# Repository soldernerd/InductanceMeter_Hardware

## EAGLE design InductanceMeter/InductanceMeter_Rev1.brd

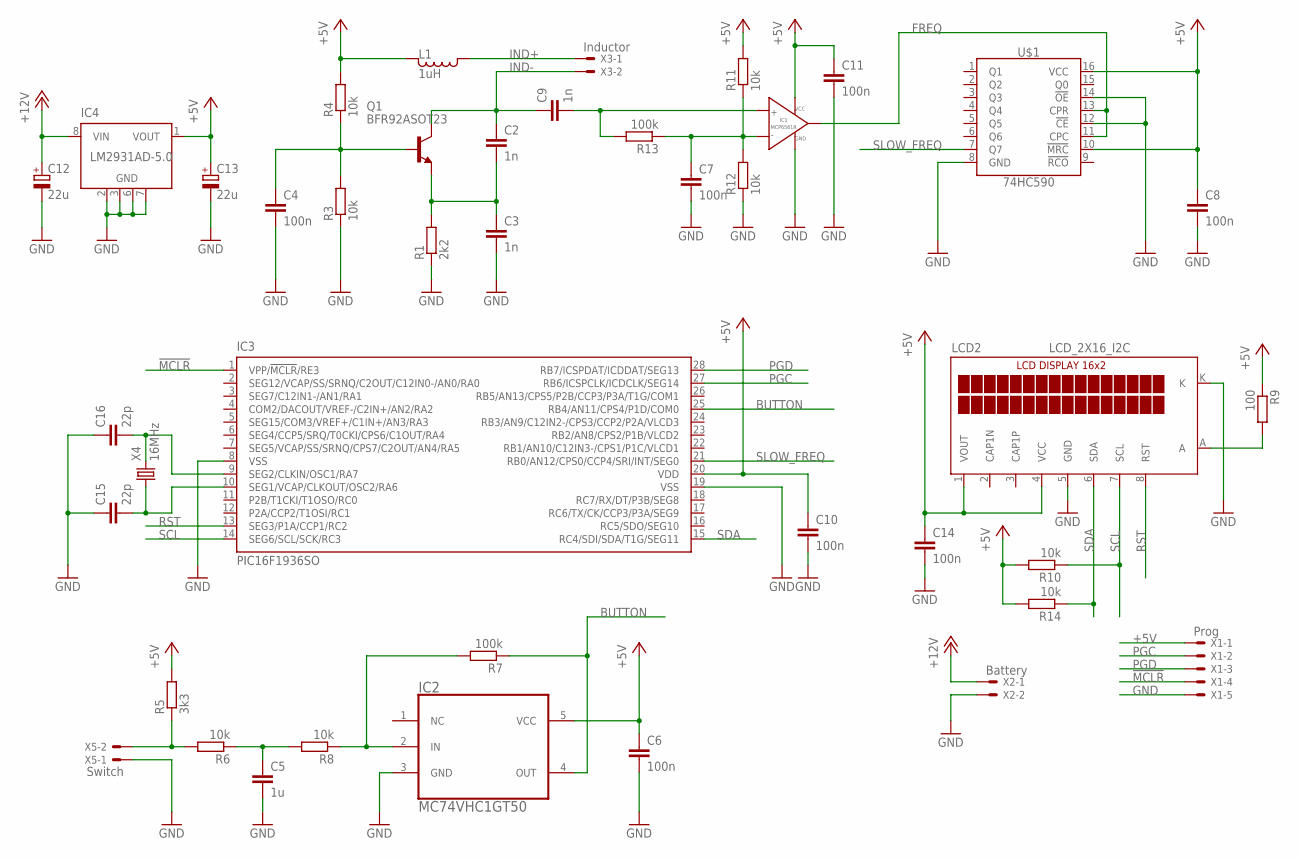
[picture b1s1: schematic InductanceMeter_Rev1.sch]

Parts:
C2, C3, C9: 1n; C0805
C4, C6, C7, C8, C10, C11, C14: 100n; C0805
C5: 1u; C0805
C12, C13: 22u; SMC_C
C15, C16: 22p; C0805
IC1: MCP6561R; SOT-23-5
IC2: MC74VHC1GT50; SOT-23-5
IC3: PIC16F1936SO; SO28W
IC4: LM2931AD-5.0; SO8
L1: 1uH; L0805
LCD2: LCD_2X16_I2C
Q1: BFR92ASOT23; SOT23
R1: 2k2; R0805
R3, R4, R6, R8, R10, R11, R12, R14: 10k; R0805
R5: 3k3; R0805
R7, R13: 100k; R0805
R9: 100; R0805
U$1: 74HC590; SO16
X1: Prog; 22-23-2051
X2: Battery; 22-23-2021
X3: Inductor; 22-23-2021
X4: 16MHz; CSM-7X-DU
X5: Switch; 22-23-2021

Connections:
!MCLR!: IC3.1 (VPP/!MCLR!/RE3), X1.4
+5V: C6.1, C8.1, C10.1, C11.1, C13.+, C14.1, IC1.2 (VCC), IC2.5 (VCC), IC3.20 (VDD), IC4.1 (VOUT), L1.2, LCD2.1 (VOUT), LCD2.4 (VCC), R4.2, R5.2, R9.1, R10.2, R11.2, R14.2, U$1.10 (!MRC!), U$1.16 (VCC), X1.1
+12V: C12.+, IC4.8 (VIN), X2.1
BUTTON: IC2.4 (OUT), IC3.25 (RB4/AN11/CPS4/P1D/COM0), R7.1
FREQ: IC1.1 (VOUT), U$1.11 (CPC), U$1.13 (CPR)
GND: C3.2, C4.2, C5.2, C6.2, C7.2, C8.2, C10.2, C11.2, C12.-, C13.-, C14.2, C15.1, C16.1, IC1.5 (GND), IC2.3 (GND), IC3.8 (VSS), IC3.19 (VSS), IC4.2 (GND), IC4.3 (GND), IC4.6 (GND), IC4.7 (GND), LCD2.5 (GND), LCD2.K, R1.1, R3.1, R12.1, U$1.8 (GND), U$1.12 (!CE!), U$1.14 (!OE!), X1.5, X2.2, X5.1
IND+: L1.1, X3.1
IND-: C2.1, C9.1, Q1.3 (C), X3.2
unnamed: C16.2, IC3.9 (SEG2/CLKIN/OSC1/RA7), X4.2
unnamed: C2.2, C3.1, Q1.2 (E), R1.2
unnamed: C4.1, Q1.1 (B), R3.2, R4.1
unnamed: LCD2.A, R9.2
unnamed: C5.1, R6.1, R8.2
unnamed: R5.1, R6.2, X5.2
unnamed: IC2.2 (IN), R7.2, R8.1
unnamed: C15.2, IC3.10 (SEG1/VCAP/CLKOUT/OSC2/RA6), X4.1
unnamed: C7.1, IC1.4 (VIN-), R11.1, R12.2, R13.1
unnamed: C9.2, IC1.3 (VIN+), R13.2
PGC: IC3.27 (RB6/ICSPCLK/ICDCLK/SEG14), X1.2
PGD: IC3.28 (RB7/ICSPDAT/ICDDAT/SEG13), X1.3
RST: IC3.13 (SEG3/P1A/CCP1/RC2), LCD2.8 (RST)
SCL: IC3.14 (SEG6/SCL/SCK/RC3), LCD2.7 (SCL), R10.1
SDA: IC3.15 (RC4/SDI/SDA/T1G/SEG11), LCD2.6 (SDA), R14.1
SLOW_FREQ: IC3.21 (RB0/AN12/CPS0/CCP4/SRI/INT/SEG0), U$1.7 (Q7)

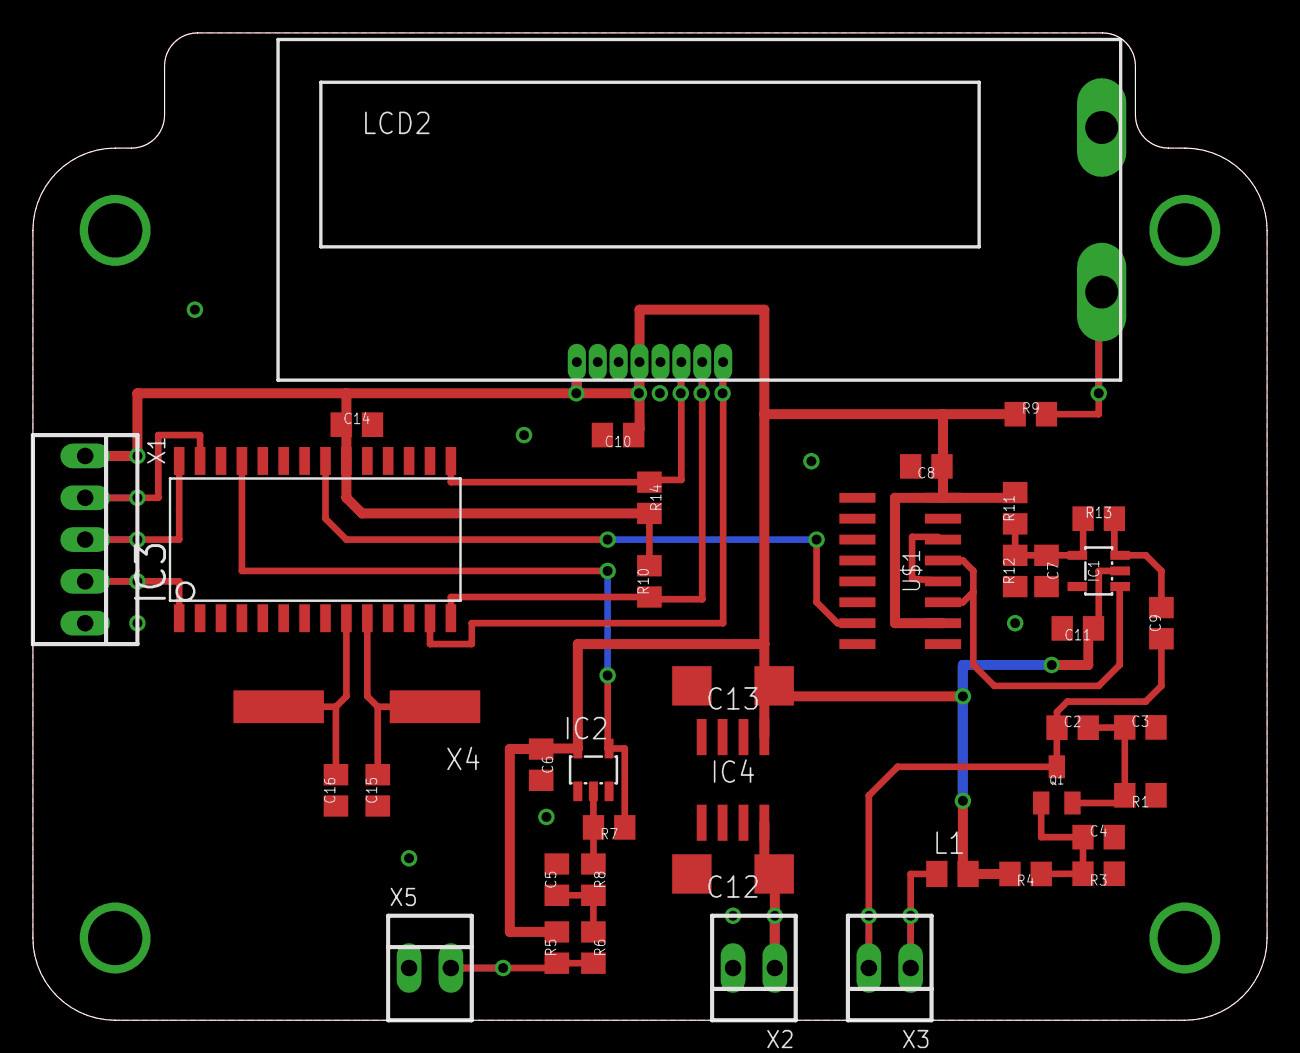
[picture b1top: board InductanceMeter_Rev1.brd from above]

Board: 2 copper layers, 75.0 x 60.0 mm, 41 parts (0 on the bottom side), 24 nets.

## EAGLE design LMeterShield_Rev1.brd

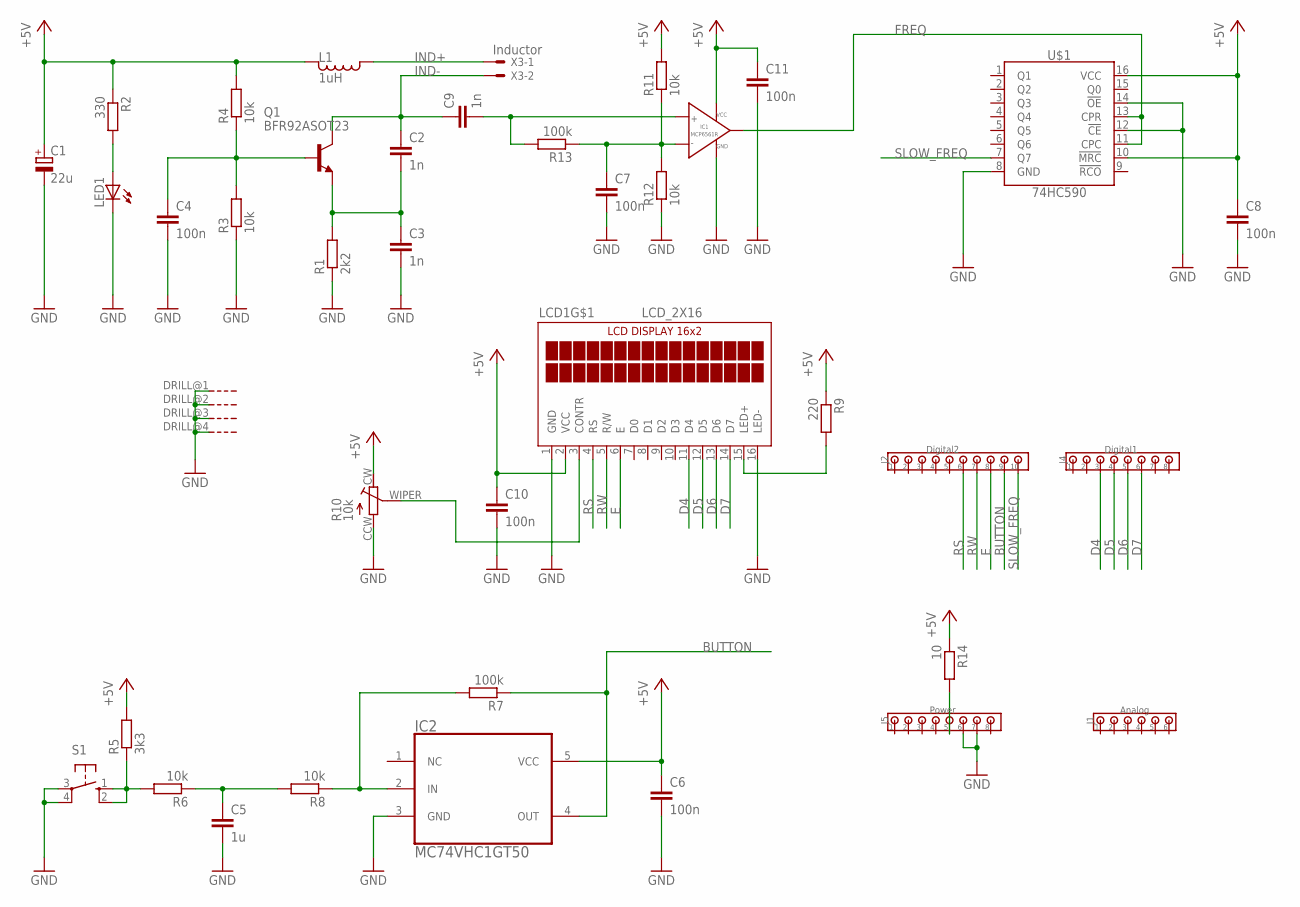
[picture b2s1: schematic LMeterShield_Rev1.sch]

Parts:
C1: 22u; SMC_C
C2, C3, C9: 1n; C0805
C4, C6, C7, C8, C10, C11: 100n; C0805
C5: 1u; C0805
IC1: MCP6561R; SOT-23-5
IC2: MC74VHC1GT50; SOT-23-5
J1: Analog; 100MIL_6X_ROUND
J2: Digital2; 100MIL_10X_ROUND
J4: Digital1; 100MIL_8X_ROUND
J5: Power; 100MIL_8X_ROUND
L1: 1uH; L0805
LCD1: LCD_2X16
LED1: LED0805
Q1: BFR92ASOT23; SOT23
R1: 2k2; R0805
R2: 330; R0805
R3, R4, R6, R8, R11, R12: 10k; R0805
R5: 3k3; R0805
R7, R13: 100k; R0805
R9: 220; R0805
R10: 10k; RTRIM3314G
R14: 10; R0805
S1: 10-XX; B3F-10XX
U$1: 74HC590; SO16
X3: Inductor; 22-23-2021

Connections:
+5V: C1.+, C6.1, C8.1, C10.1, C11.1, IC1.2 (VCC), IC2.5 (VCC), L1.2, LCD1.2 (VCC), R2.1, R4.2, R5.2, R9.1, R10.CW, R11.2, R14.1, U$1.10 (!MRC!), U$1.16 (VCC)
BUTTON: IC2.4 (OUT), J2.9, R7.1
D4: J4.3, LCD1.11 (D4)
D5: J4.4, LCD1.12 (D5)
D6: J4.5, LCD1.13 (D6)
D7: J4.6, LCD1.14 (D7)
E: J2.8, LCD1.6 (E)
FREQ: IC1.1 (VOUT), U$1.11 (CPC), U$1.13 (CPR)
GND: C1.-, C3.2, C4.2, C5.2, C6.2, C7.2, C8.2, C10.2, C11.2, IC1.5 (GND), IC2.3 (GND), J5.6, J5.7, LCD1.1 (GND), LCD1.16 (LED-), LCD1.DRILL@1 (G), LCD1.DRILL@2 (G), LCD1.DRILL@3 (G), LCD1.DRILL@4 (G), LED1.C, R1.1, R3.1, R10.CCW, R12.1, S1.3, S1.4 (P1), U$1.8 (GND), U$1.12 (!CE!), U$1.14 (!OE!)
IND+: L1.1, X3.1
IND-: C2.1, C9.1, Q1.3 (C), X3.2
unnamed: LED1.A, R2.2
unnamed: C2.2, C3.1, Q1.2 (E), R1.2
unnamed: C4.1, Q1.1 (B), R3.2, R4.1
unnamed: C5.1, R6.1, R8.2
unnamed: R5.1, R6.2, S1.1 (S), S1.2 (S1)
unnamed: IC2.2 (IN), R7.2, R8.1
unnamed: LCD1.15 (LED+), R9.2
unnamed: LCD1.3 (CONTR), R10.WIPER
unnamed: C7.1, IC1.4 (VIN-), R11.1, R12.2, R13.1
unnamed: C9.2, IC1.3 (VIN+), R13.2
RS: J2.6, LCD1.4 (RS)
RW: J2.7, LCD1.5 (R/W)
SLOW_FREQ: J2.10, U$1.7 (Q7)
VIN: J5.5, R14.2

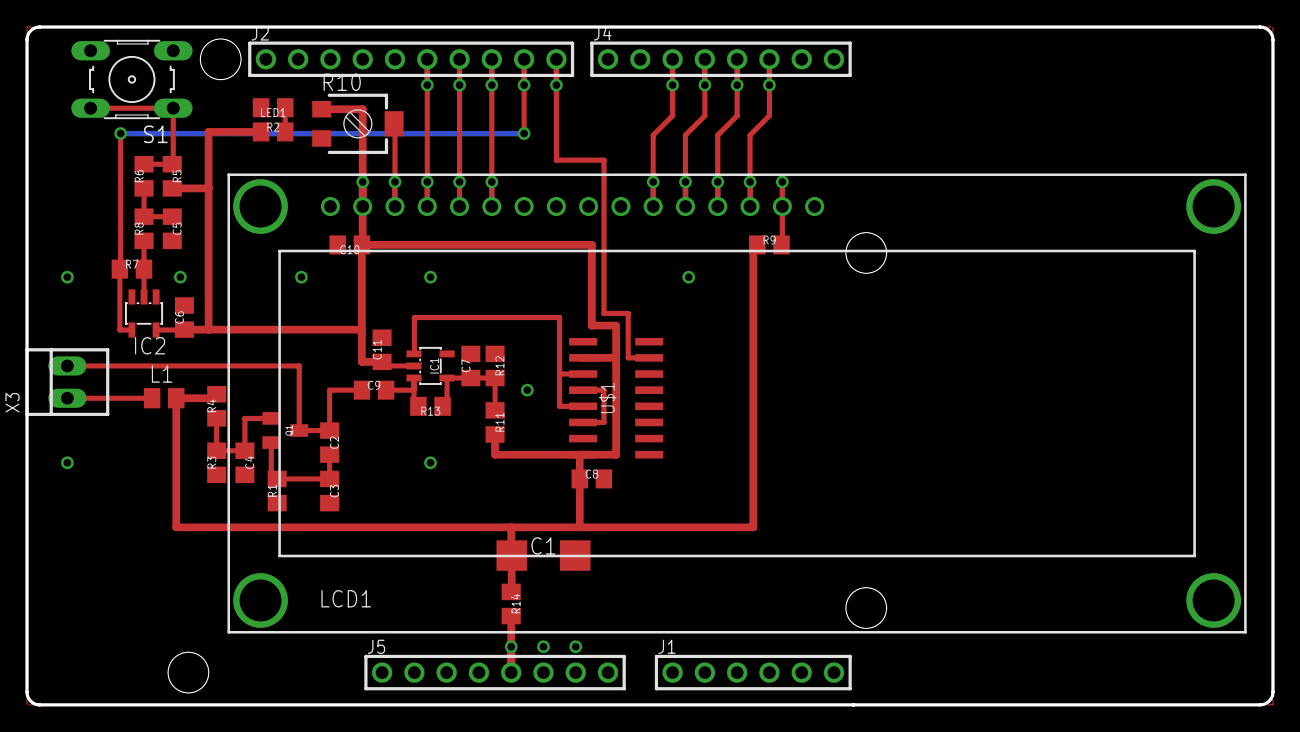
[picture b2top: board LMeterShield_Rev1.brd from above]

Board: 2 copper layers, 98.0 x 53.3 mm, 38 parts (0 on the bottom side), 25 nets.

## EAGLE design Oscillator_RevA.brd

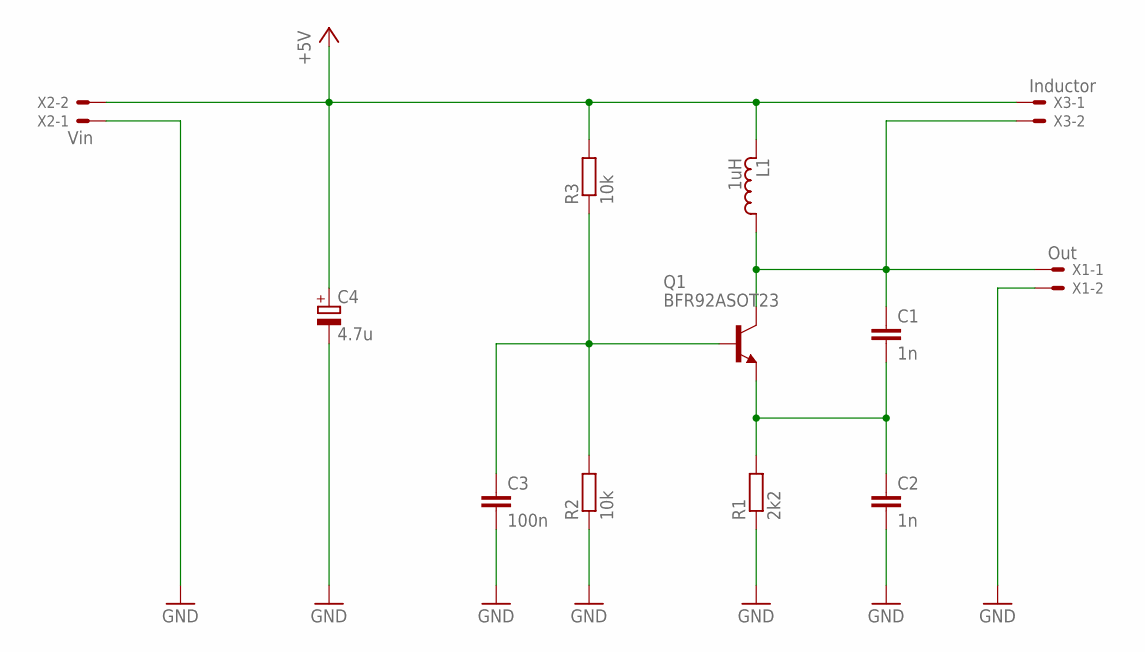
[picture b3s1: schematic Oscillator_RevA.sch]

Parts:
C1, C2: 1n; C0805
C3: 100n; C0805
C4: 4.7u; SMC_C
L1: 1uH; LPS4414
Q1: BFR92ASOT23; SOT23
R1: 2k2; R0805
R2, R3: 10k; R0805
X1: Out; 22-23-2021
X2: Vin; 22-23-2021
X3: Inductor; 22-23-2021

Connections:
+5V: C4.+, L1.2, R3.2, X2.2, X3.1
GND: C2.2, C3.2, C4.-, R1.1, R2.1, X1.2, X2.1
unnamed: C1.1, L1.1, Q1.3 (C), X1.1, X3.2
unnamed: C1.2, C2.1, Q1.2 (E), R1.2
unnamed: C3.1, Q1.1 (B), R2.2, R3.1

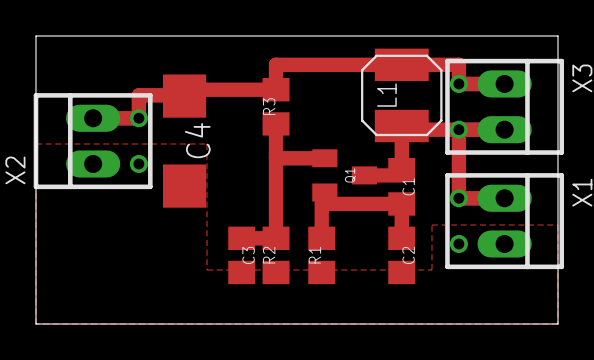
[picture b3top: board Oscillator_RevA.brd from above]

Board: 2 copper layers, 29.0 x 16.0 mm, 12 parts (0 on the bottom side), 5 nets.
